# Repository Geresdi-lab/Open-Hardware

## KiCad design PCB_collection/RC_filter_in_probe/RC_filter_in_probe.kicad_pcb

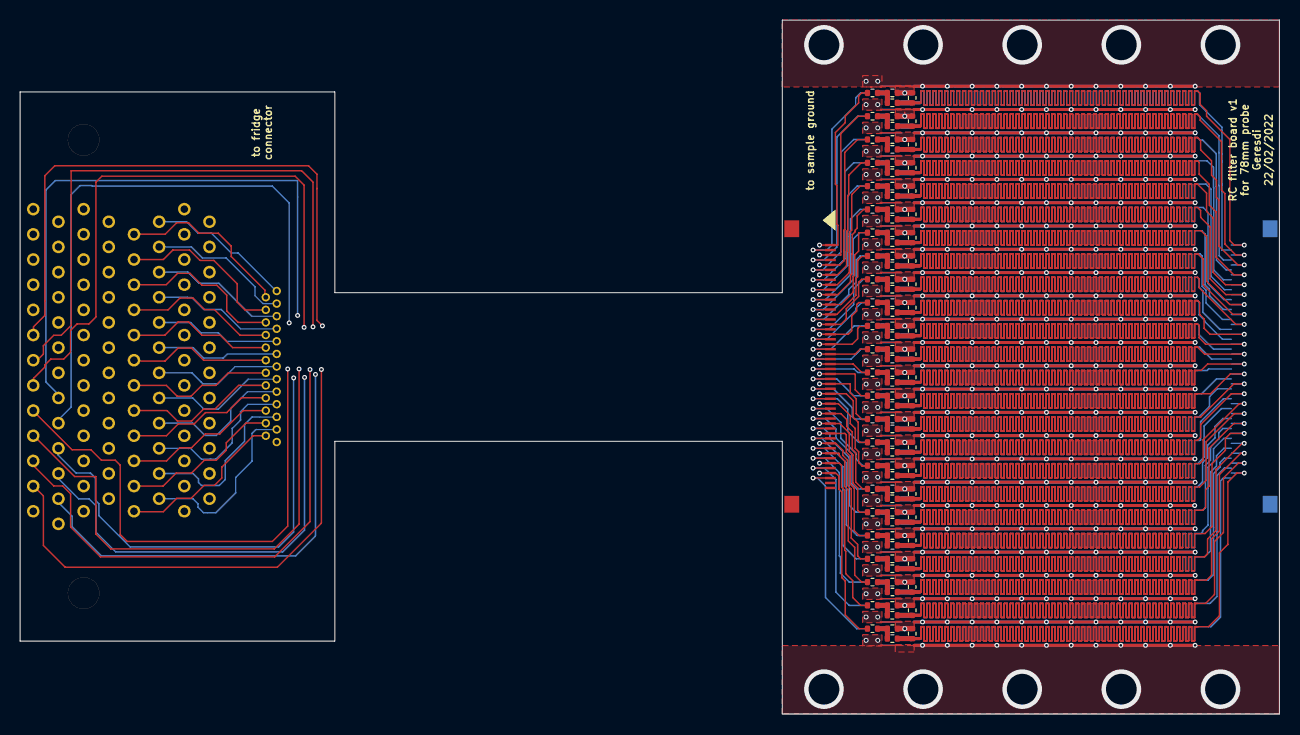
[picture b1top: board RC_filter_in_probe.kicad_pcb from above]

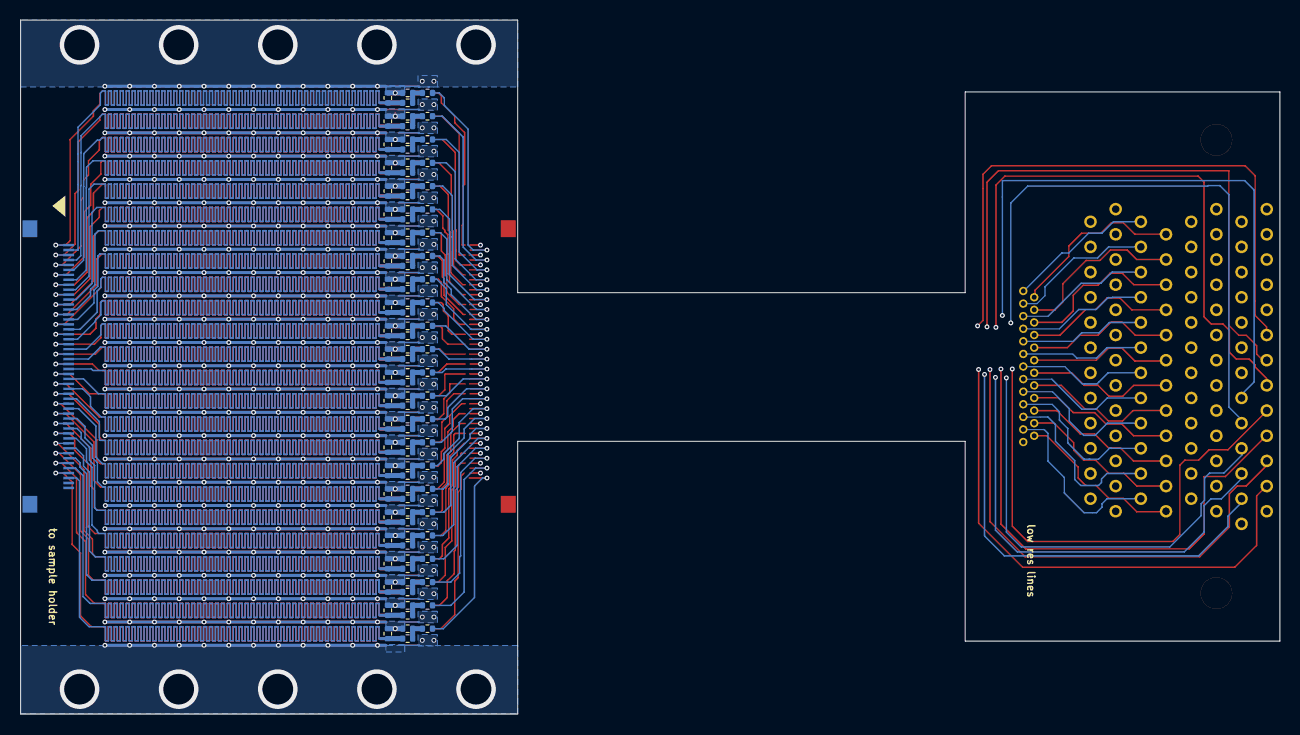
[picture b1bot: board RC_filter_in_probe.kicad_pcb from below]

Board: 4 copper layers, 127.1 x 70.0 mm, 196 parts (98 on the bottom side), 169 nets.

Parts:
C1, C2, C3, C4, C5, C6, C7, C8, C9, C10, C11, C12, C13, C14, C15, C16, C17, C18, C19, C20, C21, C22, C23, C24, C25, C26, C27, C28, C29, C30, C31, C32, C33, C34, C35, C36, C37, C38, C39, C40, C41, C42, C43, C44, C45, C46, C47, C48, C49, C50, C51, C52, C53, C54, C55, C56, C57, C58, C59, C60, C61, C62, C63, C64, C65, C66, C67, C68, C69, C70, C71, C72, C73, C74, C75, C76, C77, C78, C79, C80, C81, C82, C83, C84, C85, C86, C87, C88, C89, C90, C91, C92, C93, C94, C95, C96: C; R_0402_1005Metric
J1: Conn_02x50_Top_Bottom; microD_socket_100
J2: microD 25; microD_socket_25_vertical_NorComp
J3, J4: Conn_02x25_Top_Bottom; XF2M-5015-1A
R1, R2, R3, R4, R5, R6, R7, R8, R9, R10, R11, R12, R13, R14, R15, R16, R17, R18, R19, R20, R21, R22, R23, R24, R25, R26, R27, R28, R29, R30, R31, R32, R33, R34, R35, R36, R37, R38, R39, R40, R41, R42, R43, R44, R45, R46, R47, R48, R49, R50, R51, R52, R53, R54, R55, R56, R57, R58, R59, R60, R61, R62, R63, R64, R65, R66, R67, R68, R69, R70, R71, R72, R73, R74, R75, R76, R77, R78, R79, R80, R81, R82, R83, R84, R85, R86, R87, R88, R89, R90, R91, R92, R93, R94, R95, R96: R; R_0402_1005Metric

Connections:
/L01: J1.1, J3.1, R1.2
/L02: J1.2, J3.2, R3.2
/L03: J1.3, J3.3, R5.2
/L04: J1.4, J3.4, R7.2
/L05: J1.5, J3.5, R9.2
/L06: J1.6, J3.6, R11.2
/L07: J1.7, J3.7, R13.2
/L08: J1.8, J3.8, R15.2
/L09: J1.9, J3.9, R17.2
/L10: J1.10, J3.10, R19.2
/L11: J1.11, J3.11, R21.2
/L12: J1.12, J3.12, R23.2
/L13: J1.13, J3.13, R25.2
/L14: J1.14, J3.14, R27.2
/L15: J1.15, J3.15, R29.2
/L16: J1.16, J3.16, R31.2
/L17: J1.17, J3.17, R33.2
/L18: J1.18, J3.18, R35.2
/L19: J1.19, J3.19, R37.2
/L20: J1.20, J3.20, R39.2
/L21: J1.21, J3.21, R41.2
/L22: J1.22, J3.22, R43.2
/L23: J1.23, J3.23, R45.2
/L24: J1.24, J3.24, R47.2
/L25: J1.27, J3.25, R49.2
/L26: J1.28, J3.26, R51.2
/L27: J1.29, J3.27, R53.2
/L28: J1.30, J3.28, R55.2
/L29: J1.31, J3.29, R57.2
/L30: J1.32, J3.30, R59.2
/L31: J1.33, J3.31, R61.2
/L32: J1.34, J3.32, R63.2
/L33: J1.35, J3.33, R65.2
/L34: J1.36, J3.34, R67.2
/L35: J1.37, J3.35, R69.2
/L36: J1.38, J3.36, R71.2
/L37: J1.39, J3.37, R73.2
/L38: J1.40, J3.38, R75.2
/L39: J1.41, J3.39, R77.2
/L40: J1.42, J3.40, R79.2
/L41: J1.43, J3.41, R81.2
/L42: J1.44, J3.42, R83.2
/L43: J1.45, J3.43, R85.2
/L44: J1.46, J3.44, R87.2
/L45: J1.47, J3.45, R89.2
/L46: J1.48, J3.46, R91.2
/L47: J1.49, J3.47, R93.2
/L48: J1.50, J3.48, R95.2
/R01: J1.52, J2.1
/R02: J1.53, J2.14
/R03: J1.54, J2.2
/R04: J1.55, J2.15
/R05: J1.56, J2.3
/R06: J1.57, J2.16
/R07: J1.58, J2.4
/R08: J1.59, J2.17
/R09: J1.60, J2.5
/R10: J1.61, J2.18
/R11: J1.62, J2.6
/R12: J1.63, J2.19
/R13: J1.64, J2.7
/R14: J1.65, J2.20
/R15: J1.66, J2.8
/R16: J1.67, J2.21
/R17: J1.68, J2.9
/R18: J1.69, J2.22
/R19: J1.70, J2.10
/R20: J1.71, J2.23
/R21: J1.72, J2.11
/R22: J1.73, J2.24
/R23: J1.74, J2.12
/R24: J1.75, J2.25
/S01: C2.1, J4.1, R2.1
/S02: C4.1, J4.2, R4.1
/S03: C6.1, J4.3, R6.1
/S04: C8.1, J4.4, R8.1
/S05: C10.1, J4.5, R10.1
/S06: C12.1, J4.6, R12.1
/S07: C14.1, J4.7, R14.1
/S08: C16.1, J4.8, R16.1
/S09: C18.1, J4.9, R18.1
/S10: C20.1, J4.10, R20.1
/S11: C22.1, J4.11, R22.1
/S12: C24.1, J4.12, R24.1
/S13: C26.1, J4.13, R26.1
/S14: C28.1, J4.14, R28.1
/S15: C30.1, J4.15, R30.1
/S16: C32.1, J4.16, R32.1
/S17: C34.1, J4.17, R34.1
/S18: C36.1, J4.18, R36.1
/S19: C38.1, J4.19, R38.1
/S20: C40.1, J4.20, R40.1
/S21: C42.1, J4.21, R42.1
/S22: C44.1, J4.22, R44.1
/S23: C46.1, J4.23, R46.1
/S24: C48.1, J4.24, R48.1
/S25: C50.1, J4.25, R50.1
/S26: C52.1, J4.26, R52.1
/S27: C54.1, J4.27, R54.1
/S28: C56.1, J4.28, R56.1
/S29: C58.1, J4.29, R58.1
/S30: C60.1, J4.30, R60.1
/S31: C62.1, J4.31, R62.1
/S32: C64.1, J4.32, R64.1
/S33: C66.1, J4.33, R66.1
/S34: C68.1, J4.34, R68.1
/S35: C70.1, J4.35, R70.1
/S36: C72.1, J4.36, R72.1
/S37: C74.1, J4.37, R74.1
/S38: C76.1, J4.38, R76.1
/S39: C78.1, J4.39, R78.1
/S40: C80.1, J4.40, R80.1
/S41: C82.1, J4.41, R82.1
/S42: C84.1, J4.42, R84.1
/S43: C86.1, J4.43, R86.1
/S44: C88.1, J4.44, R88.1
/S45: C90.1, J4.45, R90.1
/S46: C92.1, J4.46, R92.1
/S47: C94.1, J4.47, R94.1
/S48: C96.1, J4.48, R96.1
GND: C1.2, C2.2, C3.2, C4.2, C5.2, C6.2, C7.2, C8.2, C9.2, C10.2, C11.2, C12.2, C13.2, C14.2, C15.2, C16.2, C17.2, C18.2, C19.2, C20.2, C21.2, C22.2, C23.2, C24.2, C25.2, C26.2, C27.2, C28.2, C29.2, C30.2, C31.2, C32.2, C33.2, C34.2, C35.2, C36.2, C37.2, C38.2, C39.2, C40.2, C41.2, C42.2, C43.2, C44.2, C45.2, C46.2, C47.2, C48.2, C49.2, C50.2, C51.2, C52.2, C53.2, C54.2, C55.2, C56.2, C57.2, C58.2, C59.2, C60.2, C61.2, C62.2, C63.2, C64.2, C65.2, C66.2, C67.2, C68.2, C69.2, C70.2, C71.2, C72.2, C73.2, C74.2, C75.2, C76.2, C77.2, C78.2, C79.2, C80.2, C81.2, C82.2, C83.2, C84.2, C85.2, C86.2, C87.2, C88.2, C89.2, C90.2, C91.2, C92.2, C93.2, C94.2, C95.2, C96.2
unnamed: C1.1, R1.1, R2.2
unnamed: C3.1, R3.1, R4.2
unnamed: C5.1, R5.1, R6.2
unnamed: C7.1, R7.1, R8.2
unnamed: C9.1, R9.1, R10.2
unnamed: C11.1, R11.1, R12.2
unnamed: C13.1, R13.1, R14.2
unnamed: C15.1, R15.1, R16.2
unnamed: C17.1, R17.1, R18.2
unnamed: C19.1, R19.1, R20.2
unnamed: C21.1, R21.1, R22.2
unnamed: C23.1, R23.1, R24.2
unnamed: C25.1, R25.1, R26.2
unnamed: C27.1, R27.1, R28.2
unnamed: C29.1, R29.1, R30.2
unnamed: C31.1, R31.1, R32.2
unnamed: C33.1, R33.1, R34.2
unnamed: C35.1, R35.1, R36.2
unnamed: C37.1, R37.1, R38.2
unnamed: C39.1, R39.1, R40.2
unnamed: C41.1, R41.1, R42.2
unnamed: C43.1, R43.1, R44.2
unnamed: C45.1, R45.1, R46.2
unnamed: C47.1, R47.1, R48.2
unnamed: C49.1, R49.1, R50.2
unnamed: C51.1, R51.1, R52.2
unnamed: C53.1, R53.1, R54.2
unnamed: C55.1, R55.1, R56.2
unnamed: C57.1, R57.1, R58.2
unnamed: C59.1, R59.1, R60.2
unnamed: C61.1, R61.1, R62.2
unnamed: C63.1, R63.1, R64.2
unnamed: C65.1, R65.1, R66.2
unnamed: C67.1, R67.1, R68.2
unnamed: C69.1, R69.1, R70.2
unnamed: C71.1, R71.1, R72.2
unnamed: C73.1, R73.1, R74.2
unnamed: C75.1, R75.1, R76.2
unnamed: C77.1, R77.1, R78.2
unnamed: C79.1, R79.1, R80.2
unnamed: C81.1, R81.1, R82.2
unnamed: C83.1, R83.1, R84.2
unnamed: C85.1, R85.1, R86.2
unnamed: C87.1, R87.1, R88.2
unnamed: C89.1, R89.1, R90.2
unnamed: C91.1, R91.1, R92.2
unnamed: C93.1, R93.1, R94.2
unnamed: C95.1, R95.1, R96.2

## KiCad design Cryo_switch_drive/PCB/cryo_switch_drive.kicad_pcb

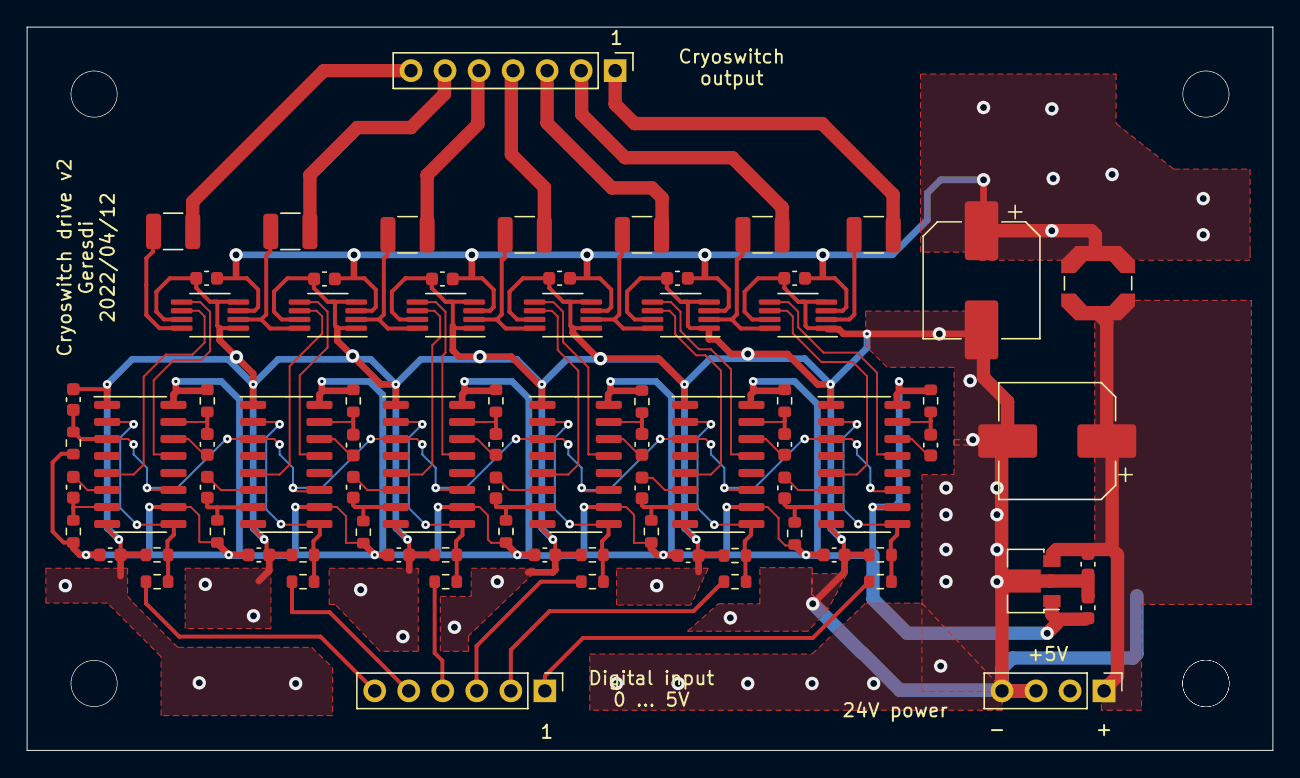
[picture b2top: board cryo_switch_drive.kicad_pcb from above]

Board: 2 copper layers, 93.0 x 54.0 mm, 78 parts (0 on the bottom side), 67 nets.

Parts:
C1, C2: 100u; CP_Elec_8x10.5
C3, C4, C5, C6, C7, C8, C9, C10, C11, C12, C13, C14, C16, C18, C19, C21, C22, C24, C25, C27, C28, C30, C31, C33, C34: 100n; C_0603_1608Metric
C15: 1u; C_0603_1608Metric
C17: 330n; C_0603_1608Metric
F1, F2, F3, F4, F5, F6, F7: MF-USHT020KX-2; R_1210_3225Metric
J1: to switch connections; PinHeader_1x07_P2.54mm_Vertical
J2: battery; PinHeader_1x04_P2.54mm_Vertical
J3: control input; PinHeader_1x06_P2.54mm_Vertical
L1: 100uH; L_Coilcraft_LPS5030
R1: 50k; R_0603_1608Metric
R2, R3, R5, R6, R8, R9, R11, R12, R14, R15, R17, R18: 150k; R_0603_1608Metric
R4, R7, R10, R13, R16, R19: 47; R_0603_1608Metric
R20, R21, R22, R23, R24, R25: 330k; R_0603_1608Metric
U1, U3, U5, U7, U9, U11: BD62105; MSOP-8_3x3mm_P0.65mm
U2, U4, U6, U8, U10, U12: 74LV221A; SOIC-16_3.9x9.9mm_P1.27mm
U13: L78L05; SOT-89-3

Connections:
+5V: C9.1, C10.1, C11.1, C12.1, C13.1, C14.1, C16.1, R1.1, R2.1, R3.1, R5.1, R6.1, R8.1, R9.1, R11.1, R12.1, R14.1, R15.1, R17.1, R18.1, U2.10, U2.16, U4.10, U4.16, U6.10, U6.16, U8.10, U8.16, U10.10, U10.16, U12.10, U12.16, U13.1
GND: C1.2, C2.2, C3.1, C4.1, C5.1, C6.1, C7.1, C8.1, C9.2, C10.2, C11.2, C12.2, C13.2, C14.2, C15.2, C16.2, C17.2, J2.3, J2.4, R20.1, R21.1, R22.1, R23.1, R24.1, R25.1, U1.1, U1.4, U1.7, U2.1, U2.8, U3.1, U3.4, U3.7, U4.1, U4.8, U5.1, U5.4, U5.7, U6.1, U6.8, U7.1, U7.4, U7.7, U8.1, U8.8, U9.1, U9.4, U9.7, U10.1, U10.8, U11.1, U11.4, U11.7, U12.1, U12.8, U13.2
unnamed: C2.1, C15.1, J2.1, L1.2, U13.3
unnamed: C18.1, R3.2, U2.7
unnamed: C18.2, U2.6
unnamed: C19.1, R2.2, U2.15
unnamed: C19.2, U2.14
unnamed: C21.1, R6.2, U4.7
unnamed: C21.2, U4.6
unnamed: C22.1, R5.2, U4.15
unnamed: C22.2, U4.14
unnamed: C24.1, R9.2, U6.7
unnamed: C24.2, U6.6
unnamed: C25.1, R8.2, U6.15
unnamed: C25.2, U6.14
unnamed: C27.1, R12.2, U8.7
unnamed: C27.2, U8.6
unnamed: C28.1, R11.2, U8.15
unnamed: C28.2, U8.14
unnamed: C30.1, R15.2, U10.7
unnamed: C30.2, U10.6
unnamed: C31.1, R14.2, U10.15
unnamed: C31.2, U10.14
unnamed: C33.1, R18.2, U12.7
unnamed: C33.2, U12.6
unnamed: C34.1, R17.2, U12.15
unnamed: C34.2, U12.14
unnamed: F1.1, J1.1
unnamed: F1.2, U1.2
unnamed: F2.1, J1.2
unnamed: F2.2, U1.8, U3.2
unnamed: F3.1, J1.3
unnamed: F3.2, U3.8, U5.2
unnamed: F4.1, J1.4
unnamed: F4.2, U5.8, U7.2
unnamed: F5.1, J1.5
unnamed: F5.2, U7.8, U9.2
unnamed: F6.1, J1.6
unnamed: F6.2, U9.8, U11.2
unnamed: F7.1, J1.7
unnamed: F7.2, U11.8
unnamed: J3.1, R4.2
unnamed: J3.2, R7.2
unnamed: J3.3, R10.2
unnamed: J3.4, R13.2
unnamed: J3.5, R16.2
unnamed: J3.6, R19.2
unnamed: R10.1, R22.2, U6.2, U6.9
unnamed: R13.1, R23.2, U8.2, U8.9
unnamed: R16.1, R24.2, U10.2, U10.9
unnamed: R19.1, R25.2, U12.2, U12.9
unnamed: R4.1, R20.2, U2.2, U2.9
unnamed: R7.1, R21.2, U4.2, U4.9
unnamed: U1.5, U2.13
unnamed: U1.6, U2.5
unnamed: U3.5, U4.13
unnamed: U3.6, U4.5
unnamed: U5.5, U6.13
unnamed: U5.6, U6.5
unnamed: U7.5, U8.13
unnamed: U7.6, U8.5
unnamed: U9.6, U10.5
unnamed: U9.5, U10.13
unnamed: U11.5, U12.13
unnamed: U11.6, U12.5
VCC: C1.1, C3.2, C4.2, C5.2, C6.2, C7.2, C8.2, L1.1, U1.3, U3.3, U5.3, U7.3, U9.3, U11.3
nRST: C17.1, R1.2, U2.3, U2.11, U4.3, U4.11, U6.3, U6.11, U8.3, U8.11, U10.3, U10.11, U12.3, U12.11

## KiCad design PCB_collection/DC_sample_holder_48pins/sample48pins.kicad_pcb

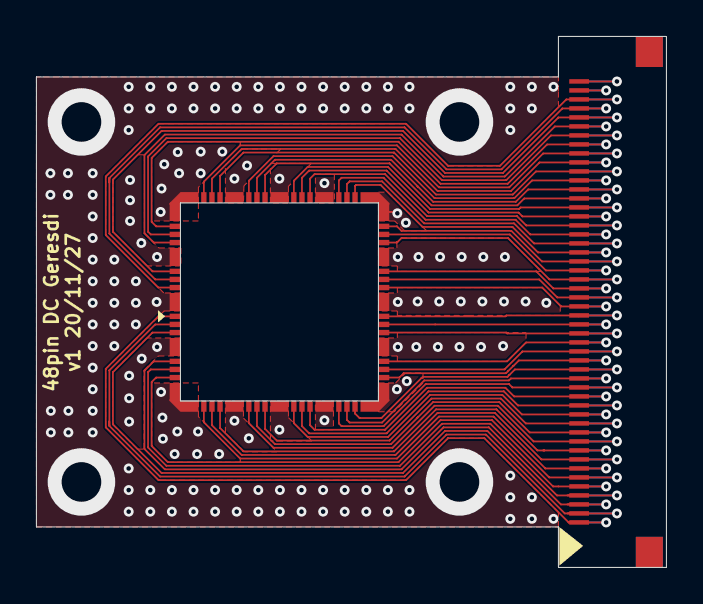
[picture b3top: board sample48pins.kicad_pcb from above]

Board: 2 copper layers, 35.0 x 29.5 mm, 3 parts (1 on the bottom side), 51 nets.

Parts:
J1: edge connector up; XF2M-5015-1A
J2: edge connector down; XF2M-5015-1A
J3: PCB bond pads; 48pin_DC

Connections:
/01: J1.1, J2.50, J3.1
/02: J1.2, J2.49, J3.2
/03: J1.3, J2.48, J3.3
/04: J1.4, J2.47, J3.4
/05: J1.5, J2.46, J3.5
/06: J1.6, J2.45, J3.6
/07: J1.7, J2.44, J3.7
/08: J1.8, J2.43, J3.8
/09: J1.9, J2.42, J3.9
/10: J1.10, J2.41, J3.10
/11: J1.11, J2.40, J3.11
/12: J1.12, J2.39, J3.12
/13: J1.13, J2.38, J3.13
/14: J1.14, J2.37, J3.14
/15: J1.15, J2.36, J3.15
/16: J1.16, J2.35, J3.16
/17: J1.17, J2.34, J3.17
/18: J1.18, J2.33, J3.18
/19: J1.19, J2.32, J3.19
/20: J1.20, J2.31, J3.20
/21: J1.21, J2.30, J3.21
/22: J1.22, J2.29, J3.22
/23: J1.23, J2.28, J3.23
/24: J1.24, J2.27, J3.24
/25: J1.25, J2.26, J3.25
/26: J1.26, J2.25, J3.26
/27: J1.27, J2.24, J3.27
/28: J1.28, J2.23, J3.28
/29: J1.29, J2.22, J3.29
/30: J1.30, J2.21, J3.30
/31: J1.31, J2.20, J3.31
/32: J1.32, J2.19, J3.32
/33: J1.33, J2.18, J3.33
/34: J1.34, J2.17, J3.34
/35: J1.35, J2.16, J3.35
/36: J1.36, J2.15, J3.36
/37: J1.37, J2.14, J3.37
/38: J1.38, J2.13, J3.38
/39: J1.39, J2.12, J3.39
/40: J1.40, J2.11, J3.40
/41: J1.41, J2.10, J3.41
/42: J1.42, J2.9, J3.42
/43: J1.43, J2.8, J3.43
/44: J1.44, J2.7, J3.44
/45: J1.45, J2.6, J3.45
/46: J1.46, J2.5, J3.46
/47: J1.47, J2.4, J3.47
/48: J1.48, J2.3, J3.48
/49: J1.49, J2.2
/50: J1.50, J2.1
GND: J3.49, J3.50, J3.51, J3.52, J3.53, J3.54, J3.55, J3.56, J3.57, J3.58, J3.59, J3.60, J3.61, J3.62, J3.63, J3.64

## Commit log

2022-09-11 added PCBs
    PCBs used in cryogenic equipment
2022-09-11 added cryo switch drive circuit
2022-09-12 change license
2022-09-12 CuPowder filter box step files
2022-09-12 probe RC filter PCB
2022-09-12 Create License
    use CERN Open Hardware Licence Version 2 - Strongly Reciprocal
